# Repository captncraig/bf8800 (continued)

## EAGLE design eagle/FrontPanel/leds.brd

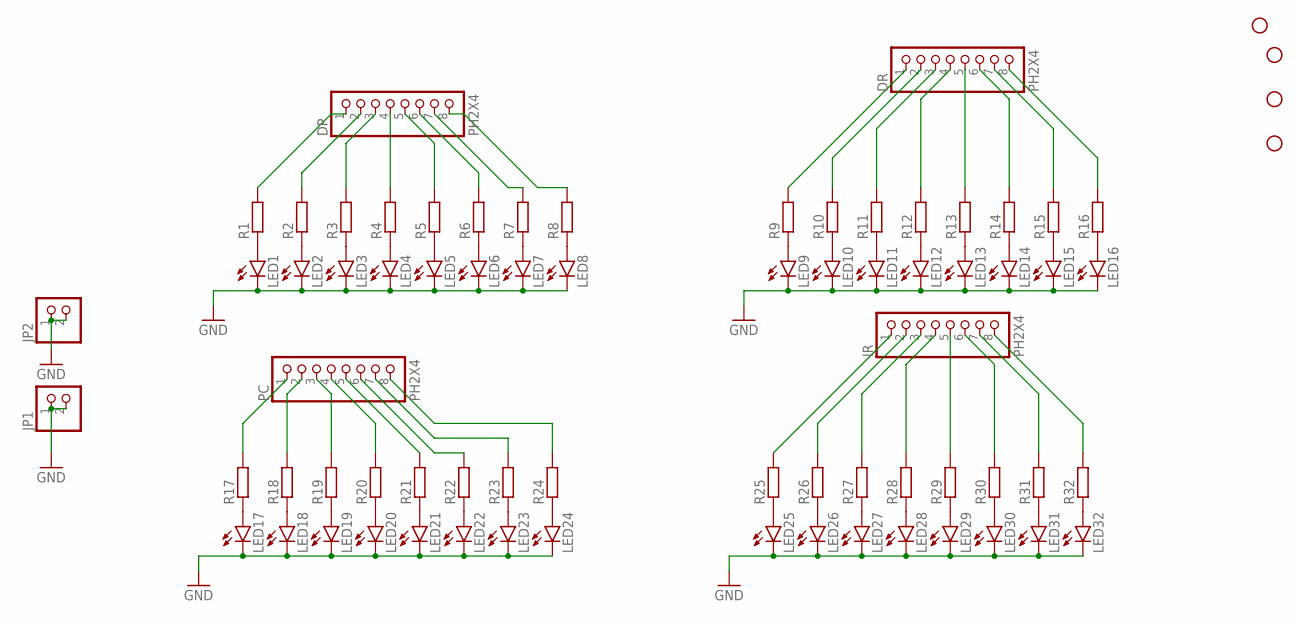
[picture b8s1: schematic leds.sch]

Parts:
DP: PH2X4; 2X04
DR: PH2X4; 2X04
H1, H2, H3, H4: STAND-OFF
IR: PH2X4; 2X04
JP1, JP2: PINHD-1X2; 1X02
LED1, LED2, LED3, LED4, LED5, LED6, LED7, LED8, LED9, LED10, LED11, LED12, LED13, LED14, LED15, LED16, LED17, LED18, LED19, LED20, LED21, LED22, LED23, LED24, LED25, LED26, LED27, LED28, LED29, LED30, LED31, LED32: LED5MM
PC: PH2X4; 2X04
R1, R2, R3, R4, R5, R6, R7, R8, R9, R10, R11, R12, R13, R14, R15, R16, R17, R18, R19, R20, R21, R22, R23, R24, R25, R26, R27, R28, R29, R30, R31, R32: R-EU_0204/5; 0204/5

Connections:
GND: JP1.1, JP1.2, JP2.1, JP2.2, LED1.K (C), LED2.K (C), LED3.K (C), LED4.K (C), LED5.K (C), LED6.K (C), LED7.K (C), LED8.K (C), LED9.K (C), LED10.K (C), LED11.K (C), LED12.K (C), LED13.K (C), LED14.K (C), LED15.K (C), LED16.K (C), LED17.K (C), LED18.K (C), LED19.K (C), LED20.K (C), LED21.K (C), LED22.K (C), LED23.K (C), LED24.K (C), LED25.K (C), LED26.K (C), LED27.K (C), LED28.K (C), LED29.K (C), LED30.K (C), LED31.K (C), LED32.K (C)
unnamed: LED1.A, R1.1
unnamed: LED2.A, R2.1
unnamed: LED3.A, R3.1
unnamed: LED4.A, R4.1
unnamed: LED5.A, R5.1
unnamed: LED6.A, R6.1
unnamed: LED7.A, R7.1
unnamed: LED8.A, R8.1
unnamed: LED9.A, R9.1
unnamed: LED10.A, R10.1
unnamed: LED11.A, R11.1
unnamed: LED12.A, R12.1
unnamed: LED13.A, R13.1
unnamed: LED14.A, R14.1
unnamed: LED15.A, R15.1
unnamed: LED16.A, R16.1
unnamed: LED17.A, R17.1
unnamed: LED18.A, R18.1
unnamed: LED19.A, R19.1
unnamed: LED20.A, R20.1
unnamed: LED21.A, R21.1
unnamed: LED22.A, R22.1
unnamed: LED23.A, R23.1
unnamed: LED24.A, R24.1
unnamed: LED25.A, R25.1
unnamed: LED26.A, R26.1
unnamed: LED27.A, R27.1
unnamed: LED28.A, R28.1
unnamed: LED29.A, R29.1
unnamed: LED30.A, R30.1
unnamed: LED31.A, R31.1
unnamed: LED32.A, R32.1
unnamed: PC.1, R17.2
unnamed: IR.1, R25.2
unnamed: DR.1, R9.2
unnamed: DP.1, R1.2
unnamed: DP.2, R2.2
unnamed: DP.3, R3.2
unnamed: DP.4, R4.2
unnamed: DP.5, R5.2
unnamed: DP.6, R6.2
unnamed: DP.7, R7.2
unnamed: DP.8, R8.2
unnamed: DR.2, R10.2
unnamed: DR.3, R11.2
unnamed: DR.4, R12.2
unnamed: DR.5, R13.2
unnamed: DR.6, R14.2
unnamed: DR.7, R15.2
unnamed: DR.8, R16.2
unnamed: IR.2, R26.2
unnamed: IR.3, R27.2
unnamed: IR.4, R28.2
unnamed: IR.5, R29.2
unnamed: IR.6, R30.2
unnamed: IR.7, R31.2
unnamed: IR.8, R32.2
unnamed: PC.2, R18.2
unnamed: PC.3, R19.2
unnamed: PC.4, R20.2
unnamed: PC.5, R21.2
unnamed: PC.6, R22.2
unnamed: PC.7, R23.2
unnamed: PC.8, R24.2

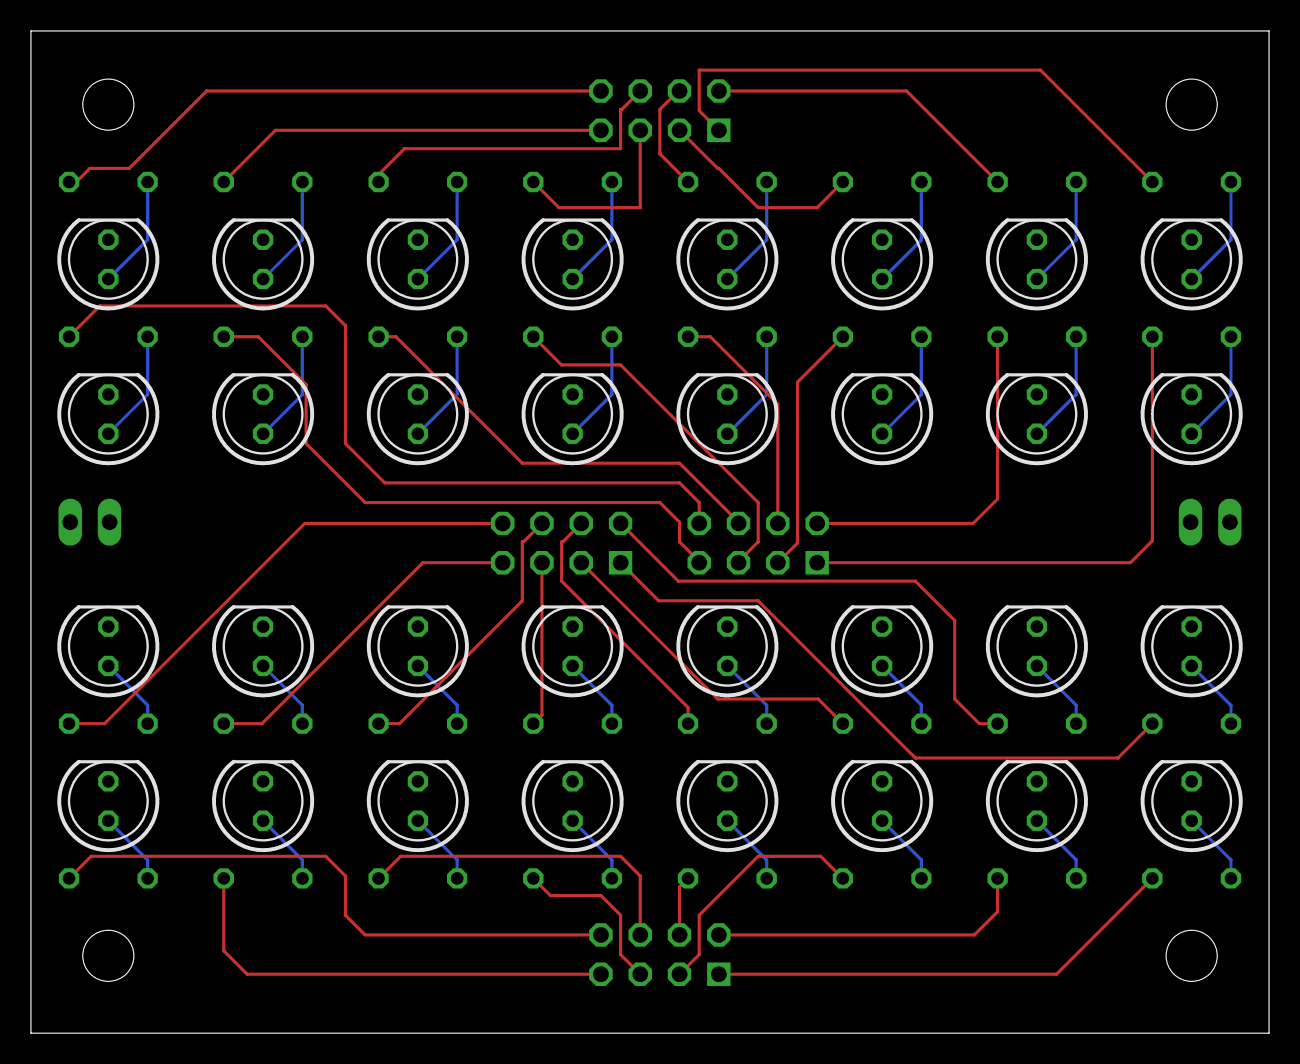
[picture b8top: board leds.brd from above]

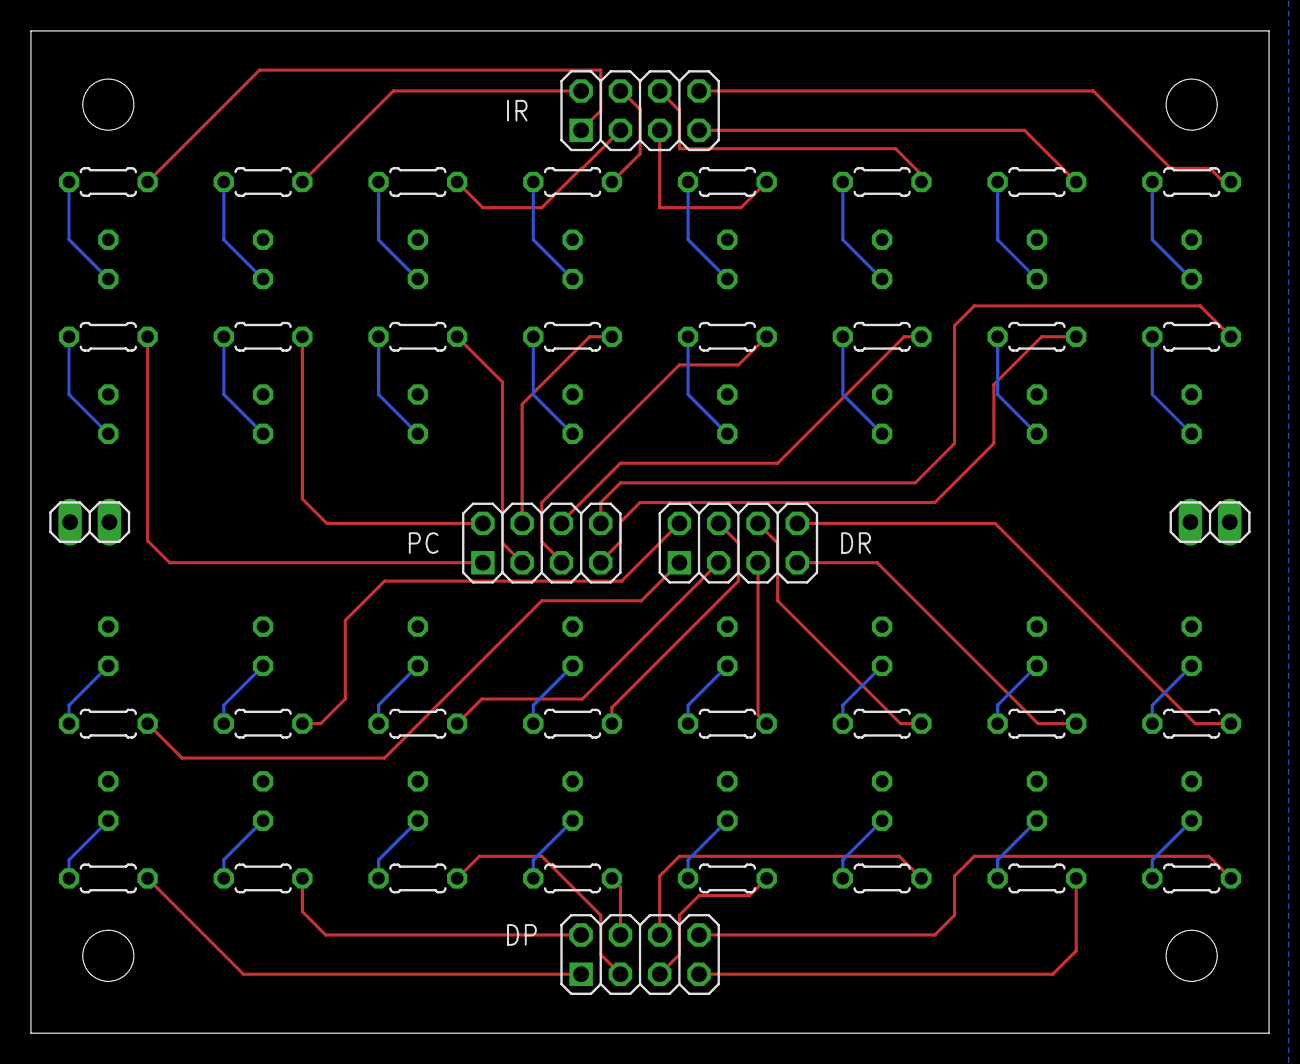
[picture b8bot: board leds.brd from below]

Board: 2 copper layers, 80.0 x 64.8 mm, 74 parts (38 on the bottom side), 65 nets.

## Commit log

2019-07-29 initial
2019-07-30 start simulator
2019-07-31 reorg into sequence
2020-02-29 Bump rake from 12.3.2 to 12.3.3
    Bumps [rake](https://github.com/ruby/rake) from 12.3.2 to 12.3.3.
    - [Release notes](https://github.com/ruby/rake/releases)
    - [Changelog](https://github.com/ruby/rake/blob/master/History.rdoc)
    - [Commits](https://github.com/ruby/rake/compare/v12.3.2...v12.3.3)
2021-07-13 Bump addressable from 2.6.0 to 2.8.0
    Bumps [addressable](https://github.com/sporkmonger/addressable) from 2.6.0 to 2.8.0.
    - [Release notes](https://github.com/sporkmonger/addressable/releases)
    - [Changelog](https://github.com/sporkmonger/addressable/blob/main/CHANGELOG.md)
    - [Commits](https://github.com/sporkmonger/addressable/compare/addressable-2.6.0...addressable-2.8.0)
    ---
    updated-dependencies:
2021-11-02 init again
2021-11-02 add schematic images
2021-11-02 opcode validator circuit thingy
2021-11-03 some work
2021-11-03 mirror board, some docks
2021-11-03 Set theme jekyll-theme-cayman
2021-11-03 add qr
2021-11-03 add gerbers
2021-11-03 test raw
2021-11-03 add scripts
2021-11-03 copy structure
2021-11-03 gerbers?
2021-11-03 stuff
2021-11-03 whaaa
2021-11-03 my tags?
2021-11-03 more
2021-11-03 moar?
2021-11-04 include?
2021-11-04 moar layers
2021-11-04 add file
2021-11-04 no drill
2021-11-04 rearrange
2021-11-04 remove extra files
